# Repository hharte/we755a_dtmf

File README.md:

# WE 755A PBX DTMF Converter

# Introduction

The Western Electric 755A PBX was designed in 1938 and supports pulse dialing only  This DTMF converter adds support for Touch-Tone dialing.  One DTMF Converter board needs to be installed in each of the three links.  The converter recognizes DTMF digits, and sets the pulse counting relays in the link to the terminal count for the number dialed.  This is not a tone to pulse converter, and operates much faster than one.

The dial plan for the 755A PBX consists of local station extensions 20-29 and 30-39.  Although this PBX supports four trunks, they are not directly accessible by stations; instead, key stations with individual trunk pickup keys are used to select the trunks.

Here is an [introductory video of the 755A PBX in operation](https://www.youtube.com/watch?v=Fxt21lnzOqg).

This project builds upon the [OKI AC125A DTMF Converter](https://github.com/hharte/ac125a_dtmf) designed several years ago.  While the OKI is an electromechanical crossbar PBX similar in some ways to the 755A, the OKI is about 40 years more modern.

# Status

Three boards have been assembled and installed in each of the 755A’s links.  They work as intended for station to station and conference calls.

# Translation

The DTMF converter employs digit translation as follows:

<table>
  <tr>
   <td>First Dialed Digit
   </td>
   <td>755A Extension
   </td>
   <td>Description
   </td>
  </tr>
  <tr>
   <td>0
   </td>
   <td>20
   </td>
   <td>Operator
   </td>
  </tr>
  <tr>
   <td>1
   </td>
   <td>-
   </td>
   <td>No operation
   </td>
  </tr>
  <tr>
   <td>2
   </td>
   <td>2x
   </td>
   <td>Direct-dialed 755A stations.
   </td>
  </tr>
  <tr>
   <td>3
   </td>
   <td>3x
   </td>
   <td>Direct-dialed 755A stations.
   </td>
  </tr>
  <tr>
   <td>4, 5, 6, 7
   </td>
   <td>-
   </td>
   <td>No operation
   </td>
  </tr>
  <tr>
   <td>8
   </td>
   <td>26
   </td>
   <td>Ringdown extensions 26, 27.
   </td>
  </tr>
  <tr>
   <td>9
   </td>
   <td>36
   </td>
   <td>Ringdown extensions 36, 37
   </td>
  </tr>
</table>

# 755A PBX Connector

<table>
  <tr>
   <td>Pin
   </td>
   <td>Description
   </td>
   <td>Ribbon Cable Color
   </td>
   <td>Cloth Wire Color
   </td>
   <td>755A Link Connection
   </td>
  </tr>
  <tr>
   <td>1,2
   </td>
   <td>GRD
   </td>
   <td>Brown/Red
   </td>
   <td>Black
   </td>
   <td>Connect to the B relay coil so the converter powers up when the link is active.
   </td>
  </tr>
  <tr>
   <td>3
   </td>
   <td>LINK_SPARE
   </td>
   <td>Orange
   </td>
   <td>
   </td>
   <td>
   </td>
  </tr>
  <tr>
   <td>4
   </td>
   <td>LINK_C1
   </td>
   <td>Yellow
   </td>
   <td>Or/Sl
   </td>
   <td>
   </td>
  </tr>
  <tr>
   <td>5
   </td>
   <td>LINK_6
   </td>
   <td>Green
   </td>
   <td>Sl/W/R
   </td>
   <td>
   </td>
  </tr>
  <tr>
   <td>6
   </td>
   <td>LINK_5-6
   </td>
   <td>Blue
   </td>
   <td>SL/W
   </td>
   <td>
   </td>
  </tr>
  <tr>
   <td>7
   </td>
   <td>LINK_4-0
   </td>
   <td>Violet
   </td>
   <td>Br/R
   </td>
   <td>
   </td>
  </tr>
  <tr>
   <td>8
   </td>
   <td>LINK_3-9
   </td>
   <td>Slate
   </td>
   <td>Br
   </td>
   <td>
   </td>
  </tr>
  <tr>
   <td>9
   </td>
   <td>LINK_2-8
   </td>
   <td>White
   </td>
   <td>Gr/R
   </td>
   <td>
   </td>
  </tr>
  <tr>
   <td>10
   </td>
   <td>LINK_1-7
   </td>
   <td>Black
   </td>
   <td>Gr
   </td>
   <td>
   </td>
  </tr>
  <tr>
   <td>11
   </td>
   <td>LINK_T3
   </td>
   <td>Brown
   </td>
   <td>Or/R
   </td>
   <td>
   </td>
  </tr>
  <tr>
   <td>12
   </td>
   <td>LINK_T2
   </td>
   <td>Red
   </td>
   <td>Or
   </td>
   <td>
   </td>
  </tr>
  <tr>
   <td>13
   </td>
   <td>N/C
   </td>
   <td>Orange
   </td>
   <td>
   </td>
   <td>
   </td>
  </tr>
  <tr>
   <td>14
   </td>
   <td>N/C
   </td>
   <td>Yellow
   </td>
   <td>
   </td>
   <td>
   </td>
  </tr>
  <tr>
   <td>15
   </td>
   <td>N/C
   </td>
   <td>Green
   </td>
   <td>
   </td>
   <td>
   </td>
  </tr>
  <tr>
   <td>16
   </td>
   <td>LINK_E
   </td>
   <td>Blue
   </td>
   <td>Blue
   </td>
   <td>
   </td>
  </tr>
  <tr>
   <td>17
   </td>
   <td>Tip
   </td>
   <td>Violet
   </td>
   <td>O/GR
   </td>
   <td>
   </td>
  </tr>
  <tr>
   <td>18
   </td>
   <td>Ring
   </td>
   <td>Slate
   </td>
   <td>O/GR-R
   </td>
   <td>
   </td>
  </tr>
  <tr>
   <td>19,20
   </td>
   <td>-24VDC
   </td>
   <td>White/Black
   </td>
   <td>Red
   </td>
   <td>-24VDC (Red)
   </td>
  </tr>
</table>

# Connection Notes

From SD-66611-01:

-BAT: Pick up from P1 relay red lead.

GRD: Pick up from B relay coil.

LINK_B: (Blue) Pick up from B relay coil (Upper left terminal.)

Tip: (Violet): Pick up T from 2mF capacitors on lower right corner (looking at from rear):

Ring: (Slate): Pick up T from 2mF capacitors on lower right corner (looking at from rear):

LINK_T2: (Red) Pick up from T2 relay coil.

LINK_T3: (Brown) Pick up from T3 relay coil.

LINK_C1: (Yellow) Pick up from C1 relay coil.

# Technical Details

## Theory of Operation

The 755A DTMF converter’s ground supply is connected to the B relay coil in the link so that the DTMF converter is only powered on when the link is active.  This is necessary so that the first and second digits dialed can be properly identified if the calling station hangs up after dialing only a single digit.

When a station goes off hook, the link allotter selects an idle link, operating the link’s B relay.  This powers up the DTMF converter, which waits for digit(s) to be dialed.  If the first dialed digit is 2 or 3, the converter waits for a second digit to be dialed and then activates the tens and units counting relays to their terminal count.  If the first digit is a digit other than 2 or 3 is dialed, the digit is handled as follows:

* 1, 4, 5, 6, or 7: Ignored
* 0, 8, 9: Translated to a 2-digit extension that is dialed immediately.

After dialing is complete, further dialing is disabled until the called station answers and hangs up again.  This is needed to prevent operation of the pulse counting relays during an established call, while also supporting conference calling.

Conference calling with the 755A works as follows:

1. The originating station calls an extension.
2. The extension answers the call, activating the E relay.
3. The originating station asks the answering station to hang up momentarily so that a conference call can be established.
4. After the called station hangs up, the originating station dials the number of an additional station to join the conference.
5. After the first digit of the called number is dialed, 

## Pulse Dialing Terminal Count Relays

### Tens Digit (2 or 3)

<table>
  <tr>
   <td>Digit
   </td>
   <td>Relays Activated
   </td>
   <td>Note
   </td>
  </tr>
  <tr>
   <td>2
   </td>
   <td>T2
   </td>
   <td>T2 activated stops dialtone.
   </td>
  </tr>
  <tr>
   <td>3
   </td>
   <td>T2 and T3
   </td>
   <td>
   </td>
  </tr>
</table>

### Units Digit (0-9)

<table>
  <tr>
   <td>Digit
   </td>
   <td>Relays Activated
   </td>
   <td>To finish dialing
   </td>
  </tr>
  <tr>
   <td>1
   </td>
   <td>C1, 1-7
   </td>
   <td>Release C1
   </td>
  </tr>
  <tr>
   <td>2
   </td>
   <td>C1, 2-8
   </td>
   <td>Release C1
   </td>
  </tr>
  <tr>
   <td>3
   </td>
   <td>C1, 3-9
   </td>
   <td>Release C1
   </td>
  </tr>
  <tr>
   <td>4
   </td>
   <td>C1, 4-0
   </td>
   <td>Release C1
   </td>
  </tr>
  <tr>
   <td>5
   </td>
   <td>C1, 5-6
   </td>
   <td>Release C1
   </td>
  </tr>
  <tr>
   <td>6
   </td>
   <td>C1, 5-6, 6
   </td>
   <td>Release C1
   </td>
  </tr>
  <tr>
   <td>7
   </td>
   <td>C1, 1-7, 6
   </td>
   <td>Release C1
   </td>
  </tr>
  <tr>
   <td>8
   </td>
   <td>C1, 2-8, 6
   </td>
   <td>Release C1
   </td>
  </tr>
  <tr>
   <td>9
   </td>
   <td>C1, 3-9, 6
   </td>
   <td>Release C1
   </td>
  </tr>
  <tr>
   <td>0
   </td>
   <td>C1, 4-0, 6
   </td>
   <td>Release C1
   </td>
  </tr>
</table>

## Inputs from 755A

<table>
  <tr>
   <td>T
   </td>
   <td colspan="3" >Tip
   </td>
  </tr>
  <tr>
   <td>R
   </td>
   <td colspan="3" >Ring
   </td>
  </tr>
  <tr>
   <td>E
   </td>
   <td colspan="3" >Call Active (Interrupt the microcontroller.)
   </td>
  </tr>
</table>

## Outputs to 755A

<table>
  <tr>
   <td>T2
   </td>
   <td colspan="3" >Tens Digit 2 (Breaks dial tone.)
   </td>
  </tr>
  <tr>
   <td>T3
   </td>
   <td colspan="3" >Tens Digit 3 (Also requires T2 activated.)
   </td>
  </tr>
  <tr>
   <td>1-7, 2-8, 3-9, 4-0, 5-6, 6
   </td>
   <td colspan="3" >Units Digit Selection
   </td>
  </tr>
  <tr>
   <td>C1
   </td>
   <td colspan="3" >Activated before Units selection relays are set, released when the digit is complete.
   </td>
  </tr>
</table>

## MT8870 DTMF Converter Outputs

<table>
  <tr>
   <td>Q3:0
   </td>
   <td colspan="3" >DTMF Digit Selection
   </td>
  </tr>
  <tr>
   <td>StB
   </td>
   <td colspan="3" >DTMF Valid Strobe (Interrupt to microcontroller.)
   </td>
  </tr>
</table>

## Bill of Materials

Online [DigiKey BOM](https://www.digikey.com/en/mylists/list/MP3JW7CHBF).  [Interactive BOM](https://html-preview.github.io/?url=https://github.com/hharte/we755a_dtmf/blob/main/hardware/bom/ibom.html).

<table>
  <tr>
   <td>Quantity
   </td>
   <td>Reference Designator
   </td>
   <td>Value
   </td>
  </tr>
  <tr>
   <td>4
   </td>
   <td>C1, C2, C4, C7
   </td>
   <td>0.1uF
   </td>
  </tr>
  <tr>
   <td>1
   </td>
   <td>C3
   </td>
   <td>0.01uF
   </td>
  </tr>
  <tr>
   <td>2
   </td>
   <td>C5, C8
   </td>
   <td>0.01uF/630V
   </td>
  </tr>
  <tr>
   <td>1
   </td>
   <td>C6
   </td>
   <td>10uF 25V
   </td>
  </tr>
  <tr>
   <td>1
   </td>
   <td>D1
   </td>
   <td>1N4148
   </td>
  </tr>
  <tr>
   <td>1
   </td>
   <td>D2
   </td>
   <td>LED
   </td>
  </tr>
  <tr>
   <td>2
   </td>
   <td>D3, D4
   </td>
   <td>1N4734A
   </td>
  </tr>
  <tr>
   <td>2
   </td>
   <td>F1, F2
   </td>
   <td>Fuse 630mA
   </td>
  </tr>
  <tr>
   <td>2
   </td>
   <td>H1, H2
   </td>
   <td>MountingHole
   </td>
  </tr>
  <tr>
   <td>1
   </td>
   <td>J1
   </td>
   <td>Conn_01x06_Male right angle
   </td>
  </tr>
  <tr>
   <td>1
   </td>
   <td>J2
   </td>
   <td>UPDI (2x3 pin header) Straight
   </td>
  </tr>
  <tr>
   <td>1
   </td>
   <td>J3
   </td>
   <td>Conn_02x10_Odd_Even
   </td>
  </tr>
  <tr>
   <td>1
   </td>
   <td>PS1
   </td>
   <td>SPBW06
   </td>
  </tr>
  <tr>
   <td>1
   </td>
   <td>R1
   </td>
   <td>100K
   </td>
  </tr>
  <tr>
   <td>1
   </td>
   <td>R2
   </td>
   <td>330K
   </td>
  </tr>
  <tr>
   <td>1
   </td>
   <td>R3
   </td>
   <td>220
   </td>
  </tr>
  <tr>
   <td>1
   </td>
   <td>R4
   </td>
   <td>52.3K 1%
   </td>
  </tr>
  <tr>
   <td>4
   </td>
   <td>R5, R6, R8, R12
   </td>
   <td>110K 1%
   </td>
  </tr>
  <tr>
   <td>1
   </td>
   <td>R7
   </td>
   <td>4.7K
   </td>
  </tr>
  <tr>
   <td>1
   </td>
   <td>R9
   </td>
   <td>220K 1%
   </td>
  </tr>
  <tr>
   <td>1
   </td>
   <td>R10
   </td>
   <td>10K
   </td>
  </tr>
  <tr>
   <td>1
   </td>
   <td>R11
   </td>
   <td>68.1K 1%
   </td>
  </tr>
  <tr>
   <td>1
   </td>
   <td>R13
   </td>
   <td>1.5K
   </td>
  </tr>
  <tr>
   <td>1
   </td>
   <td>RN1
   </td>
   <td>220
   </td>
  </tr>
  <tr>
   <td>1
   </td>
   <td>U1
   </td>
   <td>AVR128DA28-I/SP or AVR128DA28-E/SP
   </td>
  </tr>
  <tr>
   <td>1
   </td>
   <td>U2
   </td>
   <td>MT8870
   </td>
  </tr>
  <tr>
   <td>1
   </td>
   <td>U3
   </td>
   <td>H11AA1
   </td>
  </tr>
  <tr>
   <td>5
   </td>
   <td>U4, U5, U6, U7, U8
   </td>
   <td>LAA108 (or LAA110L or CLA170)
   </td>
  </tr>
  <tr>
   <td>1
   </td>
   <td>Y2
   </td>
   <td>3.579545MHZ
   </td>
  </tr>
</table>

## Arduino AVD128DA28 Configuration

# Other WE 755A Projects

[WE 755A Power Supply](https://github.com/hharte/we755a_ps)

[WE 755A Station Line Concentrator](https://github.com/hharte/we755a_slc)

[WE 755A PBX Monitor](https://github.com/hharte/we755a_mon)

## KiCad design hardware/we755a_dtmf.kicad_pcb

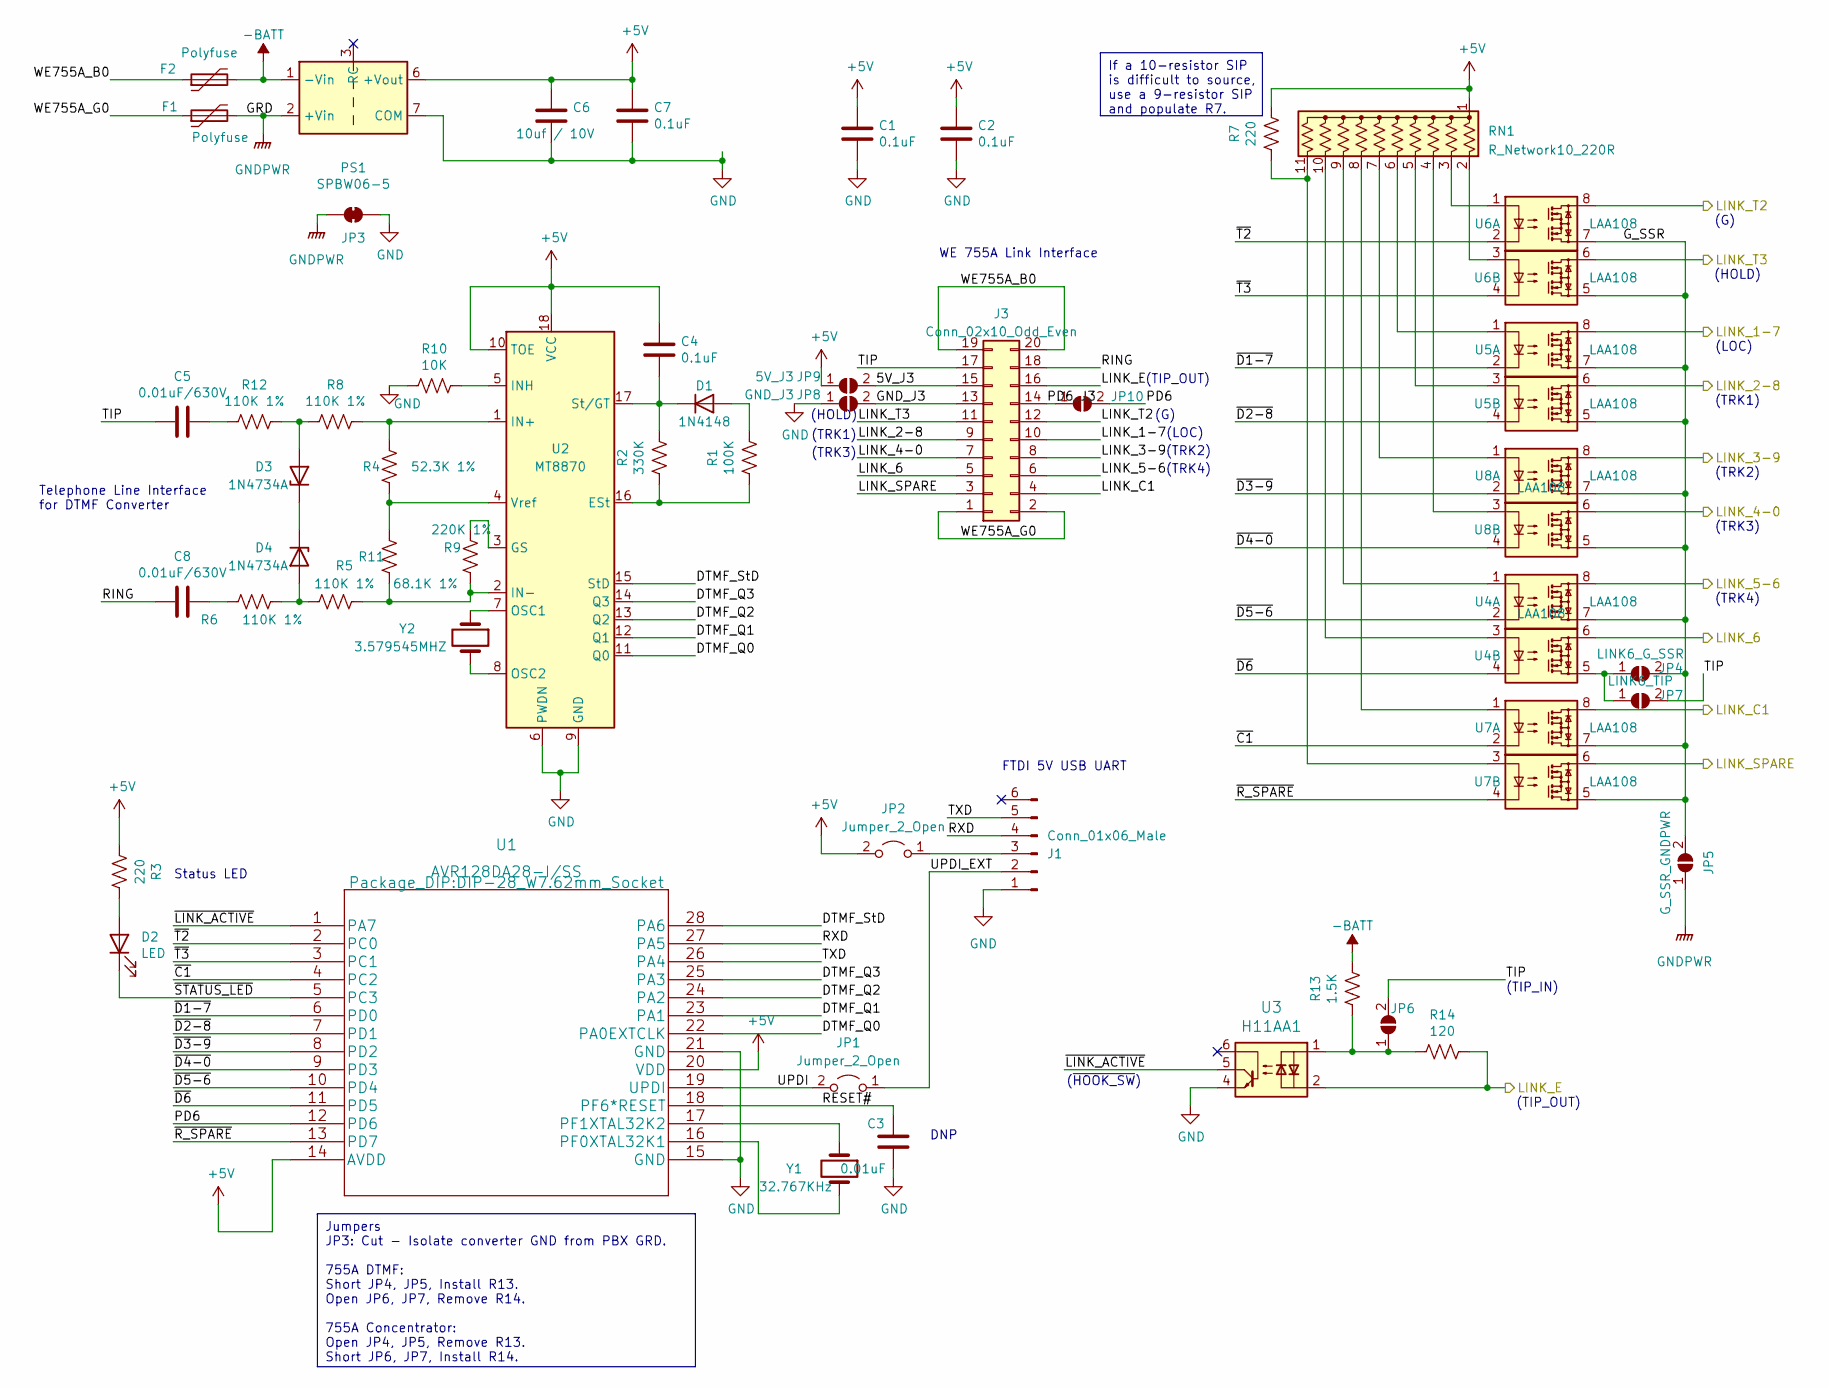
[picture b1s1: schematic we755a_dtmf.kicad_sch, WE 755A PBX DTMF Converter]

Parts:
C1, C2, C4, C7: 0.1uF; C_Disc_D3.0mm_W2.0mm_P2.50mm; MPN K104M15X7RF5TL2; Digi-Key_PN 56-K104M15X7RF5TL2CT-ND
C3: 0.01uF; C_Disc_D3.0mm_W1.6mm_P2.50mm; MPN K103K15X7RF5UL2; Digi-Key_PN BC5227CT-ND
C5, C8: 0.01uF/630V; C_Disc_D7.5mm_W5.0mm_P5.00mm; MPN RDER72J103K2K1H03B; Digi-Key_PN 490-8927-ND
C6: 10uf / 10V; C_Disc_D5.0mm_W2.5mm_P2.50mm; MPN FG14X7R1A106KRT06; Digi-Key_PN 445-173132-1-ND
D1: 1N4148; D_DO-35_SOD27_P7.62mm_Horizontal; MPN 1N4148TA; Digi-Key_PN 1N4148TACT-ND
D2: LED; LED_D5.0mm; MPN XLUR12D; Digi-Key_PN 1497-1031-ND
D3, D4: 1N4734A; D_DO-41_SOD81_P7.62mm_Horizontal; MPN 1N4734A-T50A; Digi-Key_PN 1N4734A-T50ACT-ND
F1, F2: Polyfuse; FUSE_RXEF025_LTF; MPN RXEF025; Digi-Key_PN RXEF025HF-ND
J1: Conn_01x06_Male; PinHeader_1x06_P2.54mm_Horizontal; MPN 61300611021; Digi-Key_PN 732-5339-ND
J3: Conn_02x10_Odd_Even; WE755A-DTMF; MPN SBH11-PBPC-D10-RA-BK; Digi-Key_PN S9180-ND
JP1, JP2: Jumper_2_Open; PinHeader_1x02_P2.54mm_Vertical
JP3: GRD_TIE; SolderJumper-2_P1.3mm_Bridged_Pad1.0x1.5mm
JP4: LINK6_G_SSR; SolderJumper-2_P1.3mm_Open_Pad1.0x1.5mm
JP5: G_SSR_GNDPWR; SolderJumper-2_P1.3mm_Open_Pad1.0x1.5mm
JP6: TIP_IN; SolderJumper-2_P1.3mm_Open_Pad1.0x1.5mm
JP7: LINK6_TIP; SolderJumper-2_P1.3mm_Open_Pad1.0x1.5mm
JP8: GND_J3; SolderJumper-2_P1.3mm_Open_Pad1.0x1.5mm
JP9, JP10: 5V_J3; SolderJumper-2_P1.3mm_Open_Pad1.0x1.5mm
PS1: SPBW06-5; Converter_DCDC_TRACO_TMR-xxxx_THT; MPN SPBW06G-05; Digi-Key_PN 1866-4814-ND
R1: 100K; R_Axial_DIN0207_L6.3mm_D2.5mm_P7.62mm_Horizontal; MPN CFM12JT100K; Digi-Key_PN S100KHCT-ND
R2: 330K; R_Axial_DIN0207_L6.3mm_D2.5mm_P7.62mm_Horizontal; MPN CFM12JT330K; Digi-Key_PN S330KHCT-ND
R3: 220; R_Axial_DIN0207_L6.3mm_D2.5mm_P7.62mm_Horizontal; MPN CFM14JT220R; Digi-Key_PN S220QCT-ND
R4: 52.3K 1%; R_Axial_DIN0207_L6.3mm_D2.5mm_P7.62mm_Horizontal; MPN MFR-25FBF52-52K3; Digi-Key_PN 52.3KXBK-ND
R5, R6, R8, R12: 110K 1%; R_Axial_DIN0207_L6.3mm_D2.5mm_P7.62mm_Horizontal; MPN MFR-25FBF52-110K; Digi-Key_PN 110KXBK-ND
R7: 220; R_Axial_DIN0204_L3.6mm_D1.6mm_P5.08mm_Horizontal; MPN CFM14JT220R; Digi-Key_PN S220QCT-ND
R9: 220K 1%; R_Axial_DIN0207_L6.3mm_D2.5mm_P7.62mm_Horizontal; MPN MFR-25FBF52-220K; Digi-Key_PN MFR-25FBF52-220K-ND
R10: 10K; R_Axial_DIN0207_L6.3mm_D2.5mm_P7.62mm_Horizontal; MPN CFM12JT10K0; Digi-Key_PN S10KHCT-ND
R11: 68.1K 1%; R_Axial_DIN0207_L6.3mm_D2.5mm_P7.62mm_Horizontal; MPN MFR-25FBF52-68K1; Digi-Key_PN 68.1KXBK-ND
R13: 1.5K; R_Axial_DIN0207_L6.3mm_D2.5mm_P7.62mm_Horizontal; MPN CFM12JT1K50; Digi-Key_PN S1.5KHCT-ND
R14: 120; R_Axial_DIN0207_L6.3mm_D2.5mm_P7.62mm_Horizontal; MPN CFM12JT120R; Digi-Key_PN S120HCT-ND
RN1: R_Network10_220R; R_Array_SIP11; MPN 4611X-101-221LF; Digi-Key_PN 118-4611X-101-221LF-ND
U1: AVR128DA28-I/SS; DIP-28_W7.62mm_Socket; MPN AVR128DA28-E/SP; Digi-Key_PN 150-AVR128DA28-E/SP-ND
U2: MT8870; DIP-18_W7.62mm
U3: H11AA1; DIP-6_W7.62mm; MPN H11AA1; Digi-Key_PN H11AA1M-ND
U4, U5, U6, U7, U8: LAA108; DIP-8_W7.62mm; MPN LAA108; Digi-Key_PN LAA108-ND
Y1: 32.767KHz; Crystal_Round_D2.0mm_Vertical; MPN Do not populate.; Digi-Key_PN Do not populate.
Y2: 3.579545MHZ; Crystal_HC49-U_Vertical; MPN 9B-3.579545MAAJ-B; Digi-Key_PN 887-1000-ND

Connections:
+5V: C1.1, C2.1, C4.2, C6.1, C7.1, JP2.2 (B), JP9.1 (A), PS1.6 (+Vout), R3.2, R7.1, RN1.1 (common), U1.14 (AVDD), U1.20 (VDD), U2.10 (TOE), U2.18 (VCC)
-BATT: F2.2, PS1.1 (-Vin), R13.1
/5V_J3: J3.15, JP9.2 (B)
/DTMF_Q0: U1.22 (PA0EXTCLK), U2.11 (Q0)
/DTMF_Q1: U1.23 (PA1), U2.12 (Q1)
/DTMF_Q2: U1.24 (PA2), U2.13 (Q2)
/DTMF_Q3: U1.25 (PA3), U2.14 (Q3)
/DTMF_StD: U1.28 (PA6), U2.15 (StD)
/GND_J3: J3.13, JP8.2 (B)
/G_SSR: JP4.2 (B), JP5.2 (B), U4.7, U5.5, U5.7, U6.5, U6.7, U7.5, U7.7, U8.5, U8.7
/LINK_1-7: J3.10, U5.8
/LINK_2-8: J3.9, U5.6
/LINK_3-9: J3.8, U8.8
/LINK_4-0: J3.7, U8.6
/LINK_5-6: J3.6, U4.8
/LINK_6: J3.5, U4.6
/LINK_C1: J3.4, U7.8
/LINK_E: J3.16, R14.1, U3.2
/LINK_SPARE: J3.3, U7.6
/LINK_T2: J3.12, U6.8
/LINK_T3: J3.11, U6.6
/PD6: JP10.2 (B), U1.12 (PD6)
/PD6_J3: J3.14, JP10.1 (A)
/RESET#: C3.1, U1.18 (PF6*RESET)
/RING: C8.2, J3.18
/RXD: J1.4, U1.27 (PA5)
/TIP: C5.2, J3.17, JP6.2 (B), JP7.2 (B)
/TXD: J1.5, U1.26 (PA4)
/UPDI: JP1.2 (B), U1.19 (UPDI)
/UPDI_EXT: J1.2, JP1.1 (A)
/WE755A_B0: F2.1, J3.19, J3.20
/WE755A_G0: F1.1, J3.1, J3.2
/~C1: U1.4 (PC2), U7.2
/~D1-7: U1.6 (PD0), U5.2
/~D2-8: U1.7 (PD1), U5.4
/~D3-9: U1.8 (PD2), U8.2
/~D4-0: U1.9 (PD3), U8.4
/~D5-6: U1.10 (PD4), U4.2
/~D6: U1.11 (PD5), U4.4
/~LINK_ACTIVE: U1.1 (PA7), U3.5
/~R_SPARE: U1.13 (PD7), U7.4
/~STATUS_LED: D2.1 (K), U1.5 (PC3)
/~T2: U1.2 (PC0), U6.2
/~T3: U1.3 (PC1), U6.4
GND: C1.2, C2.2, C3.2, C6.2, C7.2, J1.1, JP3.2 (B), JP8.1 (A), PS1.7 (COM), R10.2, U1.15 (GND), U1.21 (GND), U2.6 (PWDN), U2.9 (GND), U3.4
GNDPWR: F1.2, JP3.1 (A), JP5.1 (A), PS1.2 (+Vin)
unnamed: C5.1, R12.2
unnamed: C8.1, R6.2
unnamed: D1.2 (A), R1.1
unnamed: C4.1, D1.1 (K), R2.1, U2.17 (St/GT)
unnamed: D2.2 (A), R3.1
unnamed: D3.2 (A), R8.2, R12.1
unnamed: D3.1 (K), D4.1 (K)
unnamed: D4.2 (A), R5.2, R6.1
unnamed: J1.3, JP2.1 (A)
unnamed: JP4.1 (A), JP7.1 (A), U4.5
unnamed: JP6.1 (A), R13.2, R14.2, U3.1
unnamed: RN1.2 (R1), U6.3
unnamed: RN1.3 (R2), U6.1
unnamed: RN1.4 (R3), U8.3
unnamed: RN1.5 (R4), U5.3
unnamed: RN1.6 (R5), U5.1
unnamed: RN1.7 (R6), U8.1
unnamed: RN1.8 (R7), U7.1
unnamed: RN1.9 (R8), U4.1
unnamed: RN1.10 (R9), U4.3
unnamed: R7.2, RN1.11 (R10), U7.3
unnamed: U1.16 (PF0XTAL32K1), Y1.2
unnamed: U1.17 (PF1XTAL32K2), Y1.1
unnamed: R1.2, R2.2, U2.16 (ESt)
unnamed: R9.1, U2.3 (GS)
unnamed: R4.1, R8.1, U2.1 (IN+)
unnamed: R5.1, R9.2, R11.2, U2.2 (IN-)
unnamed: R10.1, U2.5 (INH)
unnamed: U2.7 (OSC1), Y2.1
unnamed: U2.8 (OSC2), Y2.2
unnamed: R4.2, R11.1, U2.4 (Vref)

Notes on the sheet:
If a 10-resistor SIP is difficult to source, use a 9-resistor SIP and populate R7.
Jumpers JP3: Cut - Isolate converter GND from PBX GRD. 755A DTMF: Short JP4, JP5, Install R13. Open JP6, JP7, Remove R14. 755A Concentrator: Open JP4, JP5, Remove R13. Short JP6, JP7, Install R14.
(HOLD)
FTDI 5V USB UART
Status LED
(~{HOOK_SW})
(TIP_OUT)
(TRK2)
(TRK4)
WE 755A Link Interface
(TIP_IN)
(G)
(TRK1)
DNP
Telephone Line Interface for DTMF Converter
(LOC)
(TRK3)

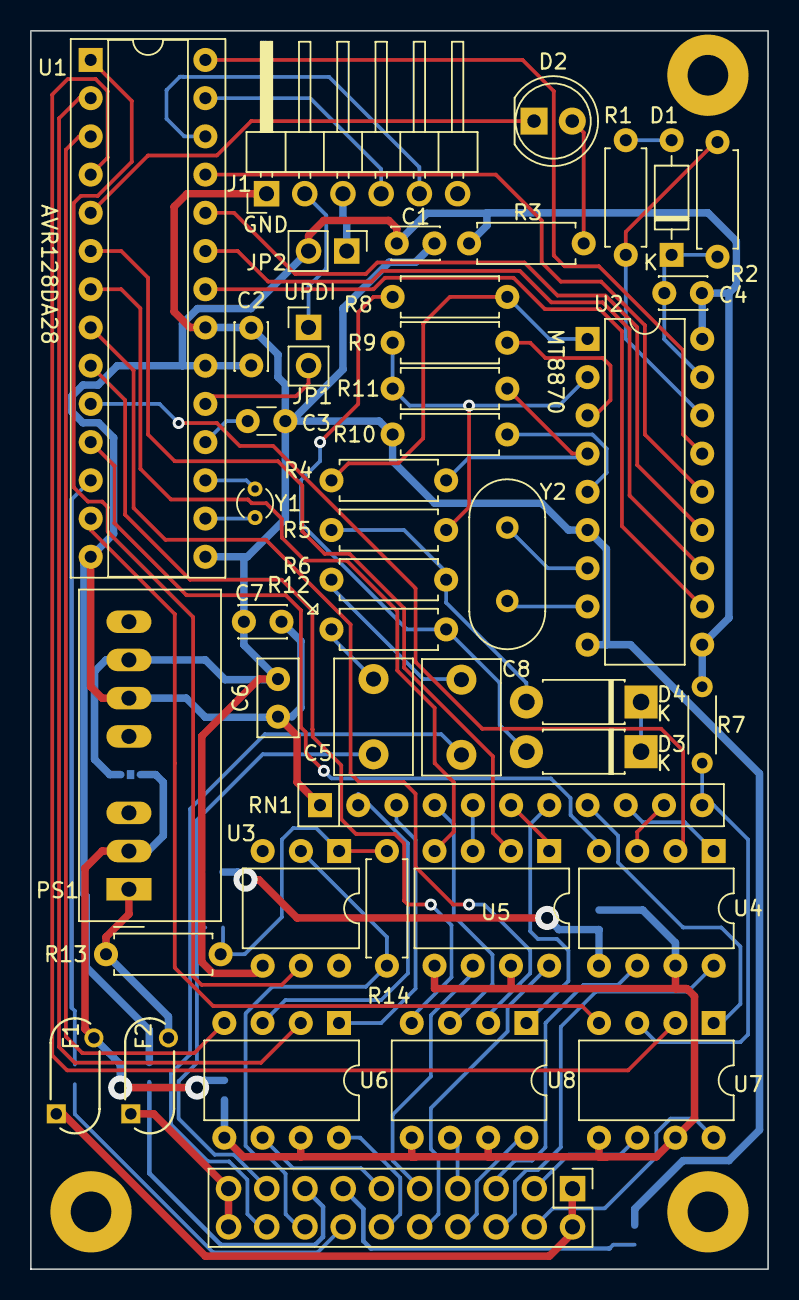
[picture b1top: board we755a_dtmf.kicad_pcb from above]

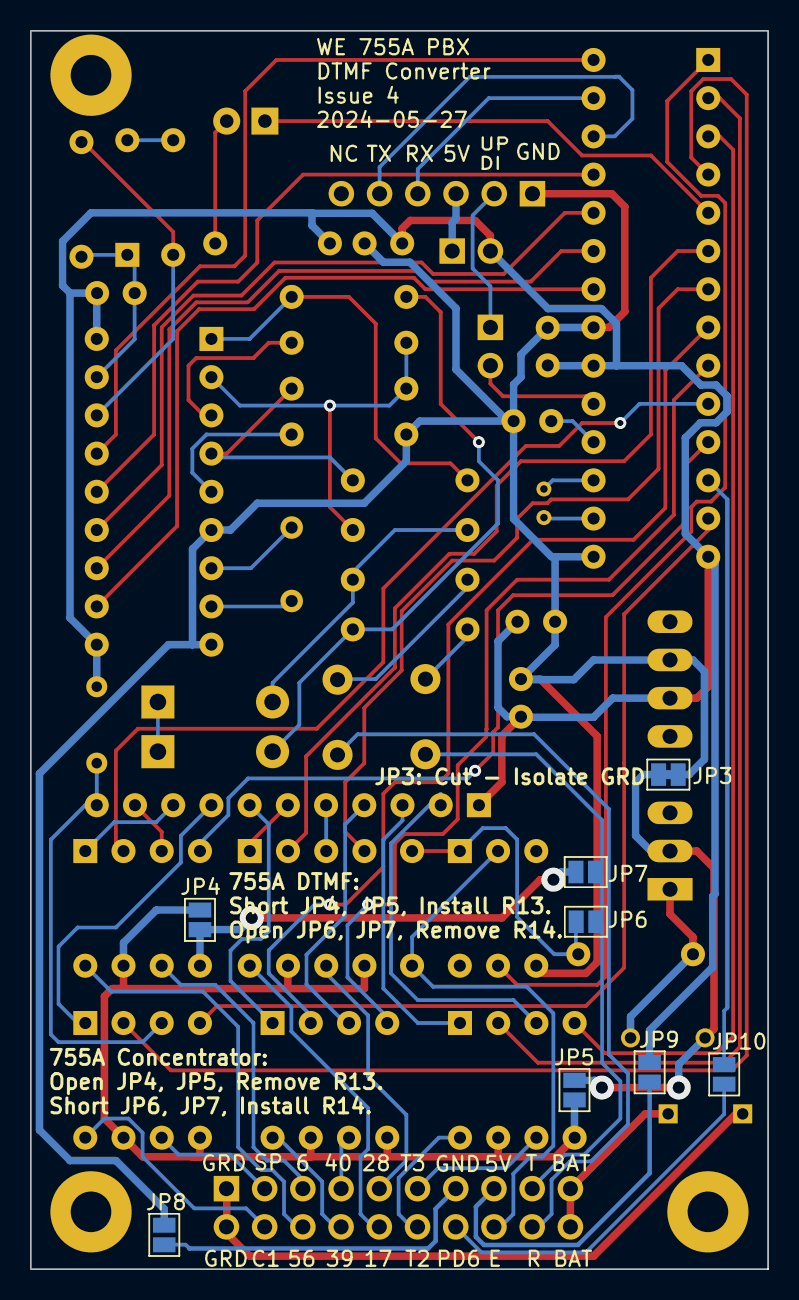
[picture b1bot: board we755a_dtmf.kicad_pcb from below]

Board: 2 copper layers, 49.0 x 82.3 mm, 52 parts (8 on the bottom side), 77 nets.

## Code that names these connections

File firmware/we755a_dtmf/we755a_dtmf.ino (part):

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 */

/* Inputs from MT8870 DTMF Receiver */
#define DTMF_Q0           0   /* PA0 */
#define DTMF_Q1           1   /* PA1 */
#define DTMF_Q2           2   /* PA2 */
#define DTMF_Q3           3   /* PA3 */
#define DTMF_StD          6   /* PA6 */

/* Outputs: Solid-State Relays driving 755A link relays, Low=On. */
#define SSR_T2            8   /* PC0 */
#define SSR_T3            9   /* PC1 */
#define SSR_C1            10  /* PC2 */

#define SSR_1_7           12  /* PD0 */
#define SSR_2_8           13  /* PD1 */
#define SSR_3_9           14  /* PD2 */
#define SSR_4_0           15  /* PD3 */
#define SSR_5_6           16  /* PD4 */
#define SSR_6             17  /* PD5 */
#define SSR_SPARE         19  /* PD7 */

#define SSR_1_7_B         (1 << 0)  /* PD0 */
#define SSR_2_8_B         (1 << 1)  /* PD1 */
#define SSR_3_9_B         (1 << 2)  /* PD2 */
#define SSR_4_0_B         (1 << 3)  /* PD3 */
#define SSR_5_6_B         (1 << 4)  /* PD4 */
#define SSR_6_B           (1 << 5)  /* PD5 */
#define SSR_SPARE_B       (1 << 7)  /* PD7 */

/* DTMF Digit to 755A Pulse Counting Relay Mapping */
const unsigned char units_relay_table[16] = {
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};

/* Inputs from 755A Link */
#define LINK_E            18  /* PD6 */

/* Output: Status LED, Low=On */
#define STATUS_LED        11  /* PIN_PC3 */

#define STATUS_LED_B      (1 << 3)

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void setup(void) {

  /* Initialize serial port */
  Serial.swap(1); /* Use PA4/PA5 for UART */
  Serial.begin(BAUD_RATE);

  VPORTC.OUT = 0xFF;
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  pinMode (SSR_5_6,     OUTPUT);
  pinMode (SSR_6,       OUTPUT);
  pinMode (SSR_SPARE,   OUTPUT);
  pinMode (STATUS_LED,  OUTPUT);

  pinMode (DTMF_StD,    INPUT);
  pinMode (DTMF_Q0,     INPUT);
  pinMode (DTMF_Q1,     INPUT);
  pinMode (DTMF_Q2,     INPUT);
  pinMode (DTMF_Q3,     INPUT);
  pinMode (LINK_E,      INPUT_PULLUP);

  takeOverTCA0();
  TCA0.SINGLE.CTRLB = TCA_SINGLE_WGMODE_NORMAL_gc;
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  TCA0.SINGLE.INTCTRL = TCA_SINGLE_OVF_bm; /* Enable timer overflow interrupt */
  TCA0.SINGLE.CTRLA = TCA_SINGLE_CLKSEL_DIV256_gc | TCA_SINGLE_ENABLE_bm;

  attachInterrupt(digitalPinToInterrupt(LINK_E), link_isr,   CHANGE);
  attachInterrupt(digitalPinToInterrupt(DTMF_StD),    DTMF_isr,   RISING);

  Serial.print("Western Electric 755A Crossbar PBX DTMF Converter v1.0\r\n");
  Serial.print("(c) 2023 Howard M. Harte - github.com/hharte/we755a_dtmf\r\n");
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
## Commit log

2023-06-25 Initial revision.
2023-06-25 755A DTMF Firmware, bench tested.
    * LED behavior:
    - Light at beginning of DTMF tone.
    - Out while idle (wait for DTMF Done)
    - On while processing relays.
    * Timing: 100ms post dial delay (before T2/T3)
    200ms hold for T2/T3, units relays, and C1.
2023-07-04 Update PCB to Rev2: No functional changes.
    * Rev 1 and Rev 2 PCBs are identical except for the silkscreen.
    * Rename LINK_B to LINK_E on schematic and layout.
    * Correct value of C1 on schematic.
2023-07-04 Add support for 755A conference call feature.
2023-07-09 Add photos of installation.
2023-07-15 Version 1.0: Working in all three 755A links.
2024-02-04 Update README with latest status.
2024-03-23 Update to KiCAD 8.0.1.
2024-04-14 Issue 3: Smaller board. * Smaller board. * Jumper options for DTMF converter and station concentrator.
2024-04-21 Update cover for Iss 3.
2024-06-02 Issue 4: Change fuses to PTCs.
2024-06-16 Change C6 from electrolytic to ceramic.
2024-06-16 Add link to we755a_mon project.

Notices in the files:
firmware/we755a_dtmf/we755a_dtmf.ino:
Copyright (c) 2023 Howard M. Harte, WZ2Q.
